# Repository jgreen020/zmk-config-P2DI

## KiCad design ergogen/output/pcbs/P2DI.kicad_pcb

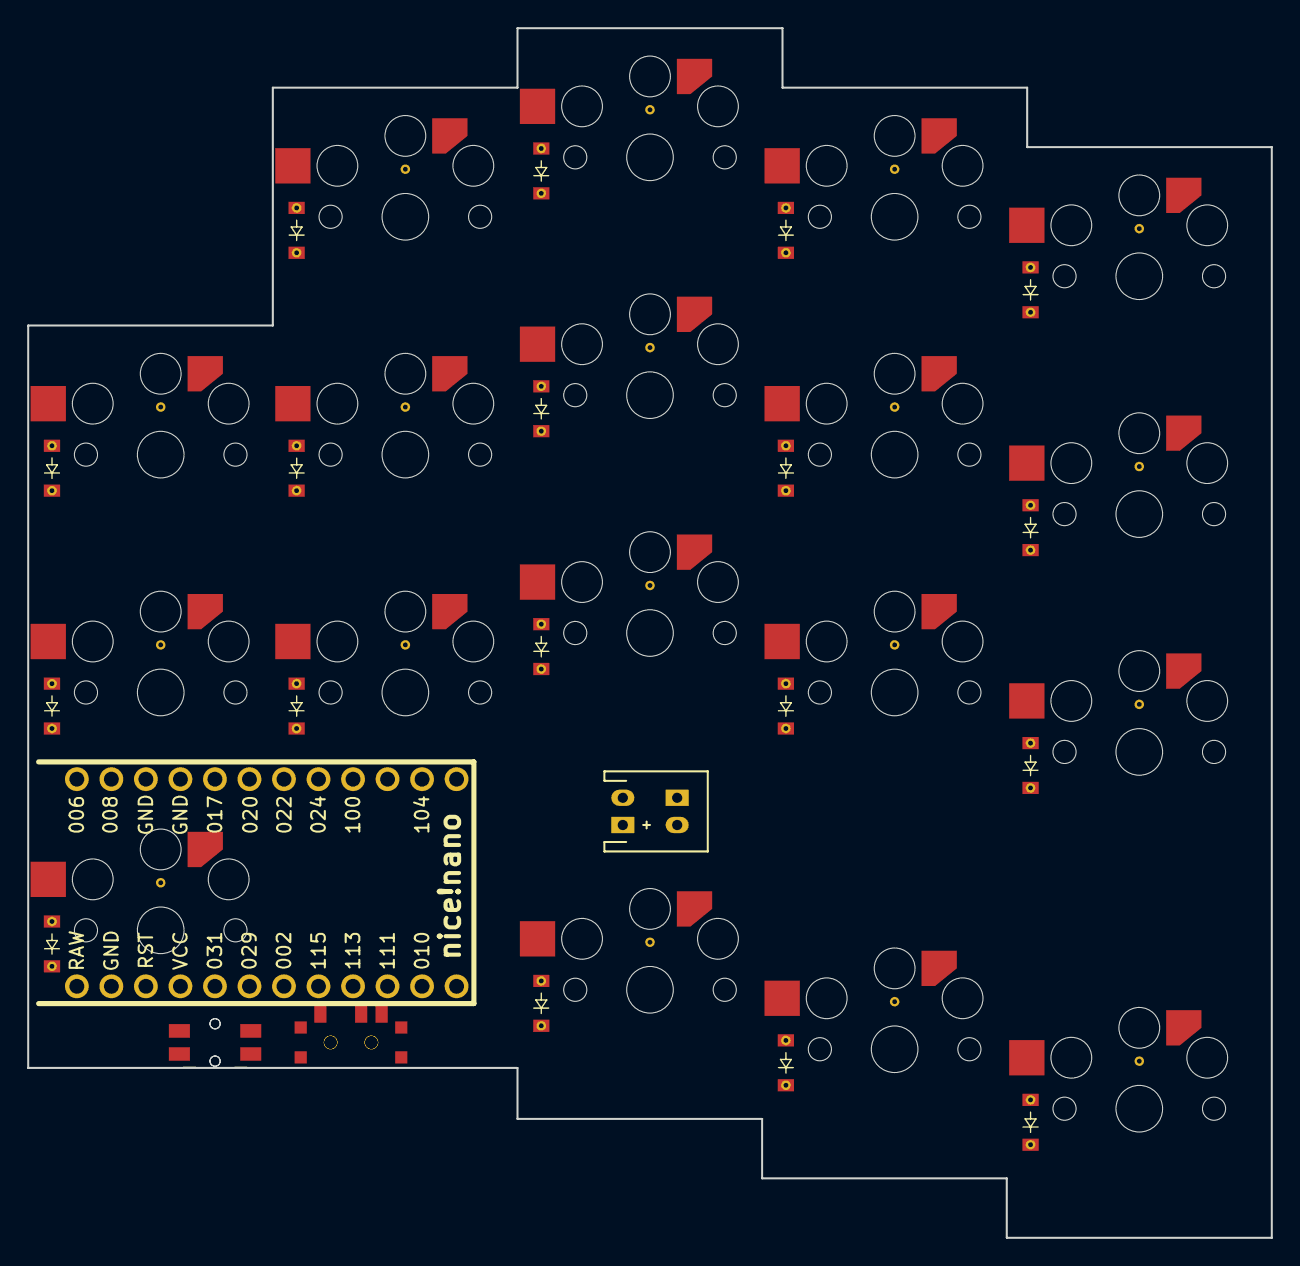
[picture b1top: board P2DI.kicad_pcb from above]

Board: 2 copper layers, 91.5 x 89.0 mm, 43 parts (0 on the bottom side), 31 nets, no tracks yet.

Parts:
B1, B2: Panasonic_EVQPUL_EVQPUC
D1, D2, D3, D4, D5, D6, D7, D8, D9, D10, D11, D12, D13, D14, D15, D16, D17, D18: ComboDiode
JST1, JST2: JST_PH_S2B-PH-K_02x2.00mm_Angled
MCU1: nice_nano
S1, S2, S3, S4, S5, S6, S7, S8, S9, S10, S11, S12, S13, S14, S15, S16, S17, S18: PG1350
T1, T2: E73_SPDT_C128955

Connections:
GND: B1.1, B2.1, JST1.2, JST2.2, MCU1.3, MCU1.4, MCU1.23
P009: D16.1, D17.1, D18.1, MCU1.13
P010: MCU1.14, S7.1, S8.1, S9.1, S16.1
P017: D3.1, D6.1, D9.1, D12.1, D15.1, MCU1.5
P020: D2.1, D5.1, D8.1, D11.1, D14.1, MCU1.6
P022: MCU1.7, S1.1, S2.1, S3.1
P024: D1.1, D4.1, D7.1, D10.1, D13.1, MCU1.8
P100: MCU1.9, S4.1, S5.1, S6.1
P111: MCU1.15, S10.1, S11.1, S12.1, S17.1
P113: MCU1.16, S13.1, S14.1, S15.1, S18.1
RAW: MCU1.24, T1.2, T2.2
RST: B1.2, B2.2, MCU1.22
first_only: D16.2, S16.2
index_bottom: D10.2, S10.2
index_home: D11.2, S11.2
index_top: D12.2, S12.2
inner_bottom: D13.2, S13.2
inner_home: D14.2, S14.2
inner_top: D15.2, S15.2
middle_bottom: D7.2, S7.2
middle_home: D8.2, S8.2
middle_top: D9.2, S9.2
pinky_bottom: D1.2, S1.2
pinky_home: D2.2, S2.2
pinky_top: D3.2, S3.2
pos: JST1.1, JST2.1, T1.1, T2.1
ring_bottom: D4.2, S4.2
ring_home: D5.2, S5.2
ring_top: D6.2, S6.2
second_only: D17.2, S17.2
third_only: D18.2, S18.2

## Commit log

2024-11-15 Initial Commit, ZMK Setup
2024-11-15 Starting Configuration for the custom shield
2024-11-15 Continue config
2024-11-16 Hopefully this works
2024-11-16 add actions maybe
2024-11-16 Actually build the right boards
2024-11-16 Made it look more like the caldera
2024-12-05 ConnectivityChanges
2025-03-07 compatibility issues
2025-03-07 i messed up
2025-03-07 moving keymap file so i can edit it in the keymap editor
2025-06-09 adding ergogen, KiCad, and case files
2026-04-30 Updated P2DI.keymap
2026-04-30 zephyr 4.1 update
2026-04-30 add Q to nav layer
2026-04-30 wait longer for deep sleep
2026-04-30 typo
2026-04-30 revert e8dec75928ec2c28d06f3223007842c579bc7bbb
2026-04-30 pin ZMK v2.0
